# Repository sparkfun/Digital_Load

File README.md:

Digital_Load
==========================================

A PSoC-based digital load that allows the user to set a desired current which will be maintained despite changes in voltage supply.
Check on the [SparkFun Enginursday post](https://www.sparkfun.com/news/2434) about the project build or the [SparkFun Variable Load Kit](https://www.sparkfun.com/products/14449) that uses this design. 

License Information
-------------------

This product is _**open source**_! 

Please review the LICENSE.md file for license information. 

If you have any questions or concerns on licensing, please contact techsupport@sparkfun.com.

Distributed as-is; no warranty is given.

- Your friends at SparkFun.

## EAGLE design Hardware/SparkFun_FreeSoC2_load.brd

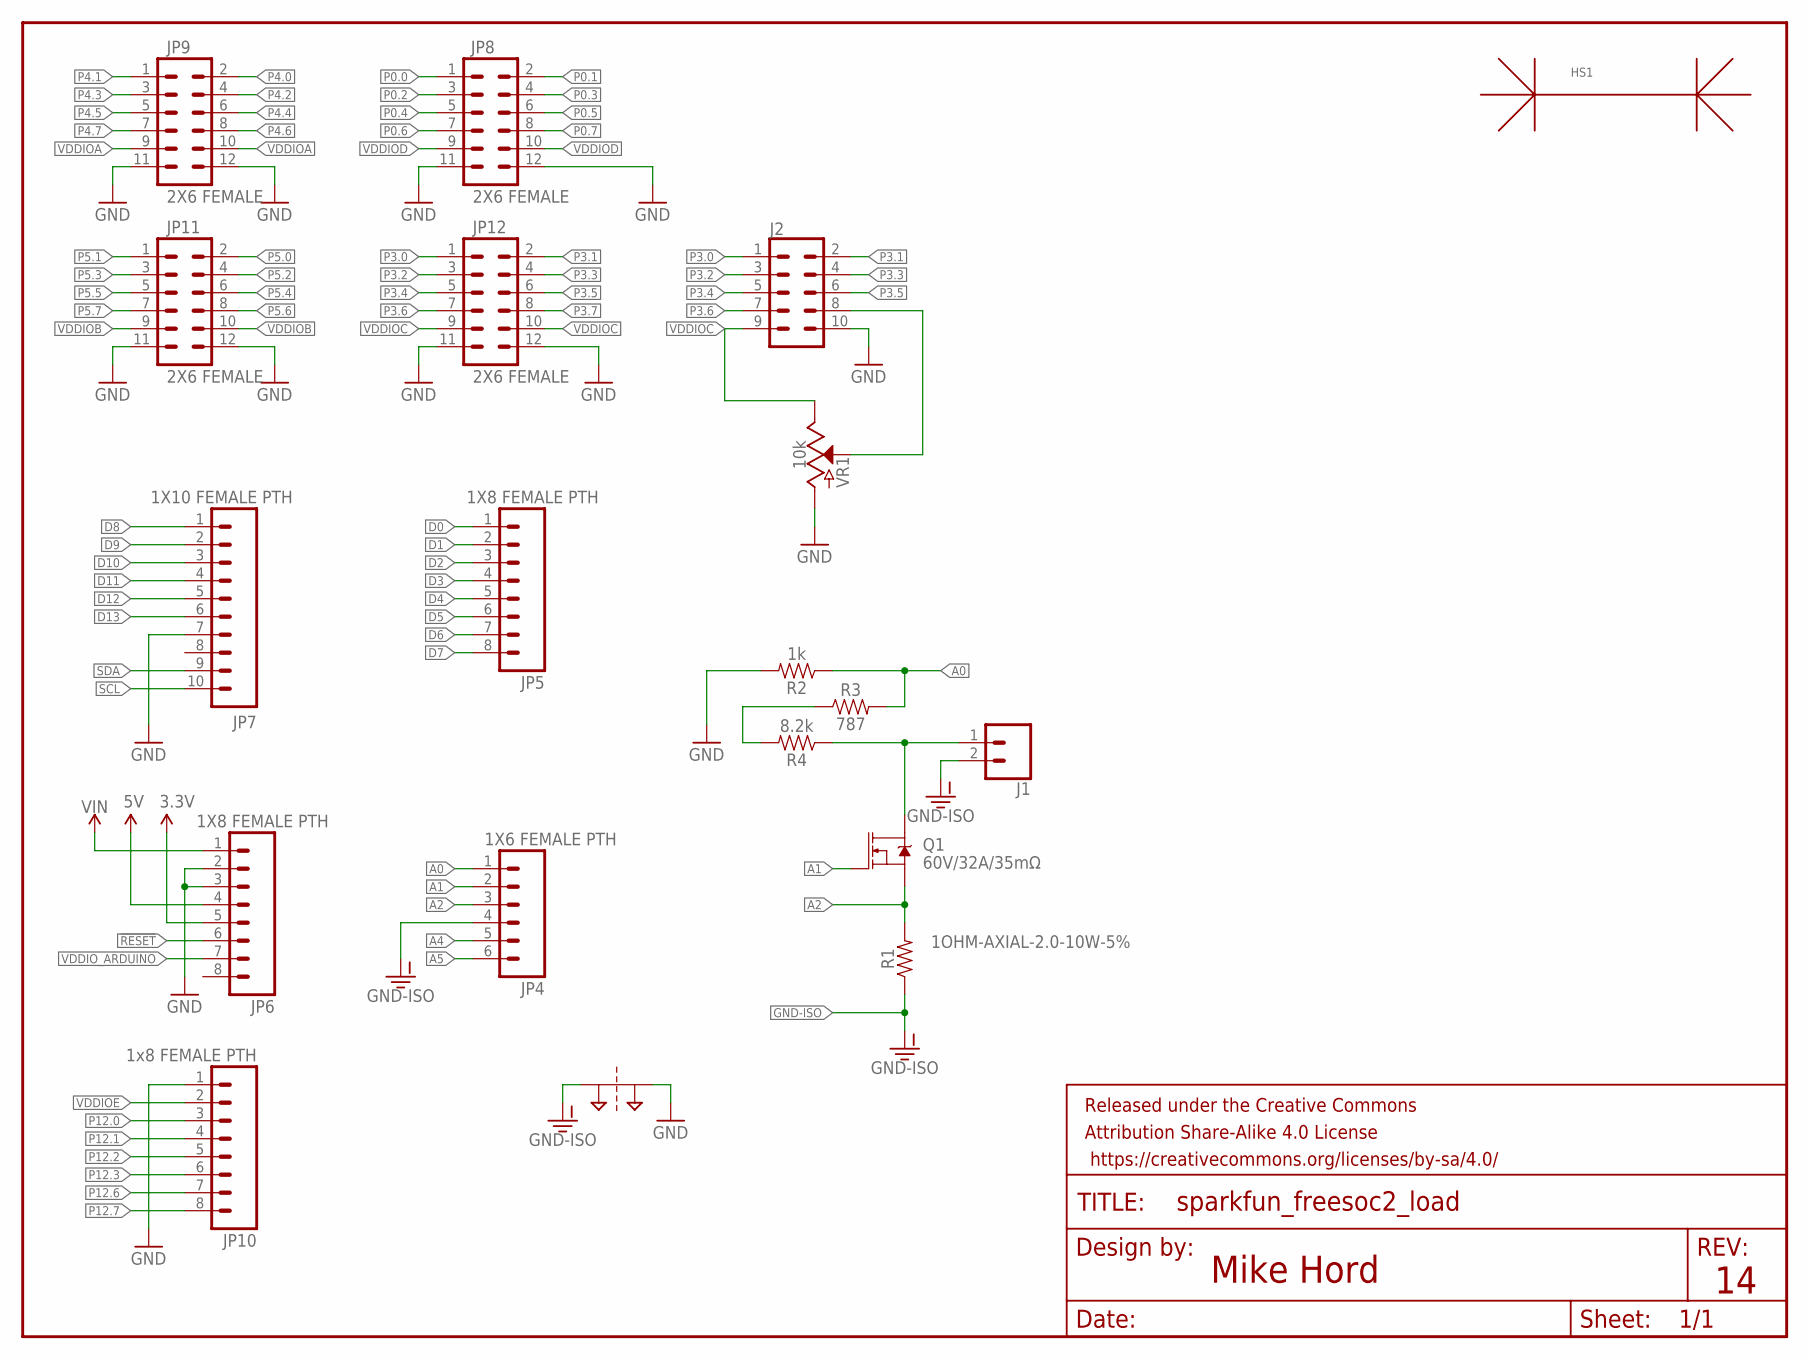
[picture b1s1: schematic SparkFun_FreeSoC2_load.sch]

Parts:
FRAME3: FRAME-LETTERNO_PACKAGE; DUMMY
HS1: HEATSINKPRT-9576; HEATSINK_PRT-9576
J1: CONN_023.5MM; SCREWTERMINAL-3.5MM-2
J2: CONN_05X2SHD; 2X5-SHROUDED
JP4: 1X6 FEMALE PTH; 1X06-SIP_LOCK
JP5, JP6: 1X8 FEMALE PTH; 1X08_LOCK
JP7: 1X10 FEMALE PTH; 1X10_LOCK
JP8, JP9, JP11, JP12: 2X6 FEMALE; 2X6
JP10: 1x8 FEMALE PTH; 1X08_LOCK
Q1: 60V/32A/35mΩ; TO220V
R1: 1OHM-AXIAL-2.0-10W-5%; AXIAL-2.0
R2: 1k; 0603
R3: 787; 0603
R4: 8.2k; 0603
SUPPLY2: 2PT_GND_TIE
VR1: 10k; POT-PTH-ALPS

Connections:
3.3V: JP6.5
5V: JP6.4
!RESET: JP6.6
A0: JP4.1, R2.1, R3.2
A1: JP4.2, Q1.1 (G)
A2: JP4.3, Q1.3 (S), R1.P$2 (2)
A4: JP4.5
A5: JP4.6
D0: JP5.1
D1: JP5.2
D2: JP5.3
D3: JP5.4
D4: JP5.5
D5: JP5.6
D6: JP5.7
D7: JP5.8
D8: JP7.1
D9: JP7.2
D10: JP7.3
D11: JP7.4
D12: JP7.5
D13: JP7.6
GND: J2.10, JP6.2, JP6.3, JP7.7, JP8.11, JP8.12, JP9.11, JP9.12, JP10.1, JP11.11, JP11.12, JP12.11, JP12.12, R2.2, SUPPLY2.P$1, VR1.P$3 (A)
GND-ISO: J1.2, JP4.4, R1.P$1 (1), SUPPLY2.P$2
unnamed: J1.1, Q1.2 (D), R4.1
unnamed: R3.1, R4.2
unnamed: J2.8, VR1.P$2 (S)
P0.0: JP8.1
P0.1: JP8.2
P0.2: JP8.3
P0.3: JP8.4
P0.4: JP8.5
P0.5: JP8.6
P0.6: JP8.7
P0.7: JP8.8
P3.0: J2.1, JP12.1
P3.1: J2.2, JP12.2
P3.2: J2.3, JP12.3
P3.3: J2.4, JP12.4
P3.4: J2.5, JP12.5
P3.5: J2.6, JP12.6
P3.6: J2.7, JP12.7
P3.7: JP12.8
P4.0: JP9.2
P4.1: JP9.1
P4.2: JP9.4
P4.3: JP9.3
P4.4: JP9.6
P4.5: JP9.5
P4.6: JP9.8
P4.7: JP9.7
P5.0: JP11.2
P5.1: JP11.1
P5.2: JP11.4
P5.3: JP11.3
P5.4: JP11.6
P5.5: JP11.5
P5.6: JP11.8
P5.7: JP11.7
P12.0: JP10.3
P12.1: JP10.4
P12.2: JP10.5
P12.3: JP10.6
P12.6: JP10.7
P12.7: JP10.8
SCL: JP7.10
SDA: JP7.9
VDDIOA: JP9.9, JP9.10
VDDIOB: JP11.9, JP11.10
VDDIOC: J2.9, JP12.9, JP12.10, VR1.P$1 (E)
VDDIOD: JP8.9, JP8.10
VDDIOE: JP10.2
VDDIO_ARDUINO: JP6.7
VIN: JP6.1

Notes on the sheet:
Mike Hord

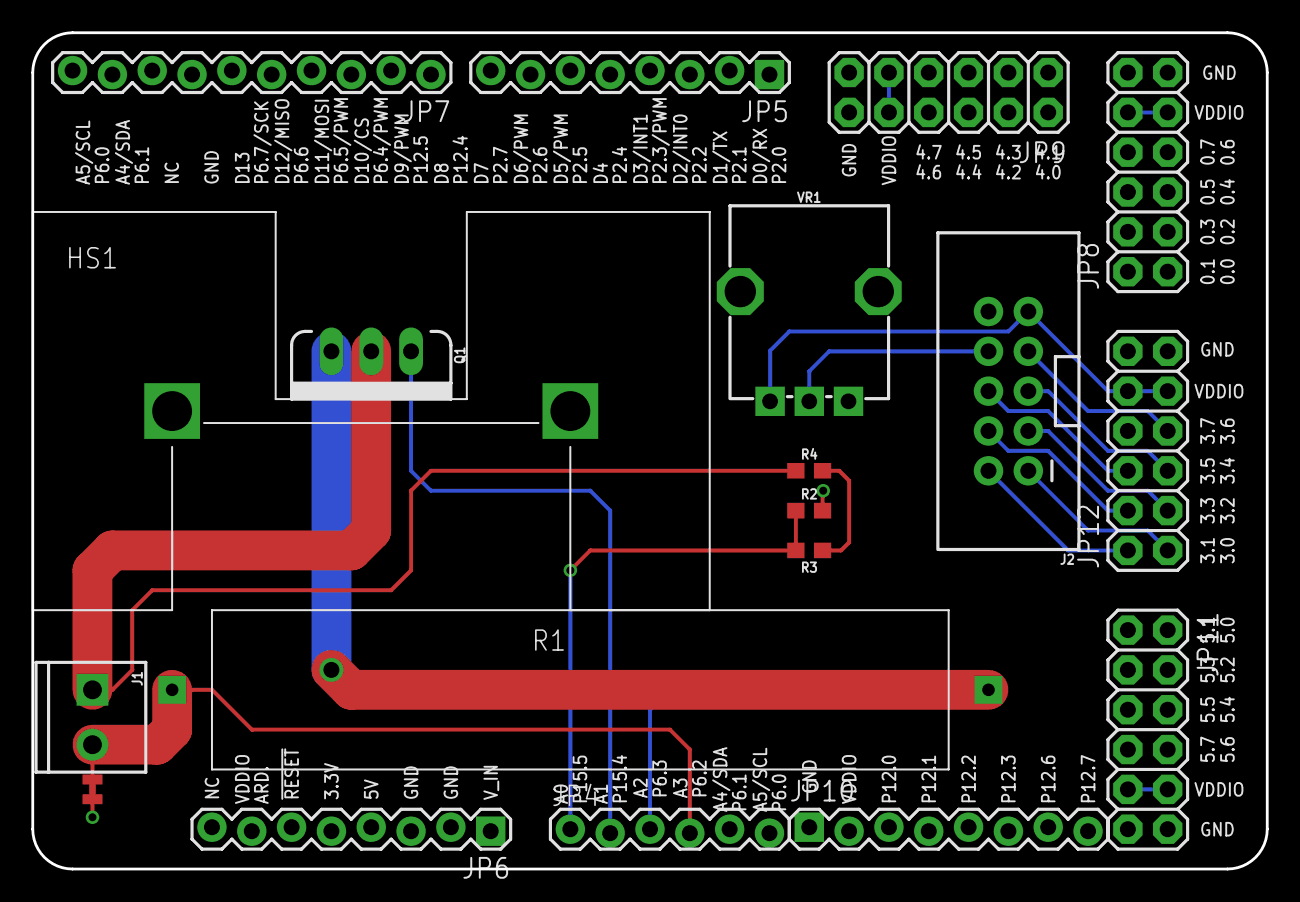
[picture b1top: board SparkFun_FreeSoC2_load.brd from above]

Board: 4 copper layers, 78.7 x 53.3 mm, 21 parts (0 on the bottom side), 19 nets.

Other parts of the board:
U$2: CREATIVE_COMMONS@1

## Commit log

2018-02-22 Create new file

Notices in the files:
parts and their libraries:
SparkFun-Aesthetics: Licensing: Creative Commons ShareAlike 4.0 International - https://creativecommons.org/licenses/by-sa/4.0
SparkFun-Aesthetics: Released under the Creative Commons Attribution Share-Alike 4.0 License
SparkFun-Aesthetics: https://creativecommons.org/licenses/by-sa/4.0
